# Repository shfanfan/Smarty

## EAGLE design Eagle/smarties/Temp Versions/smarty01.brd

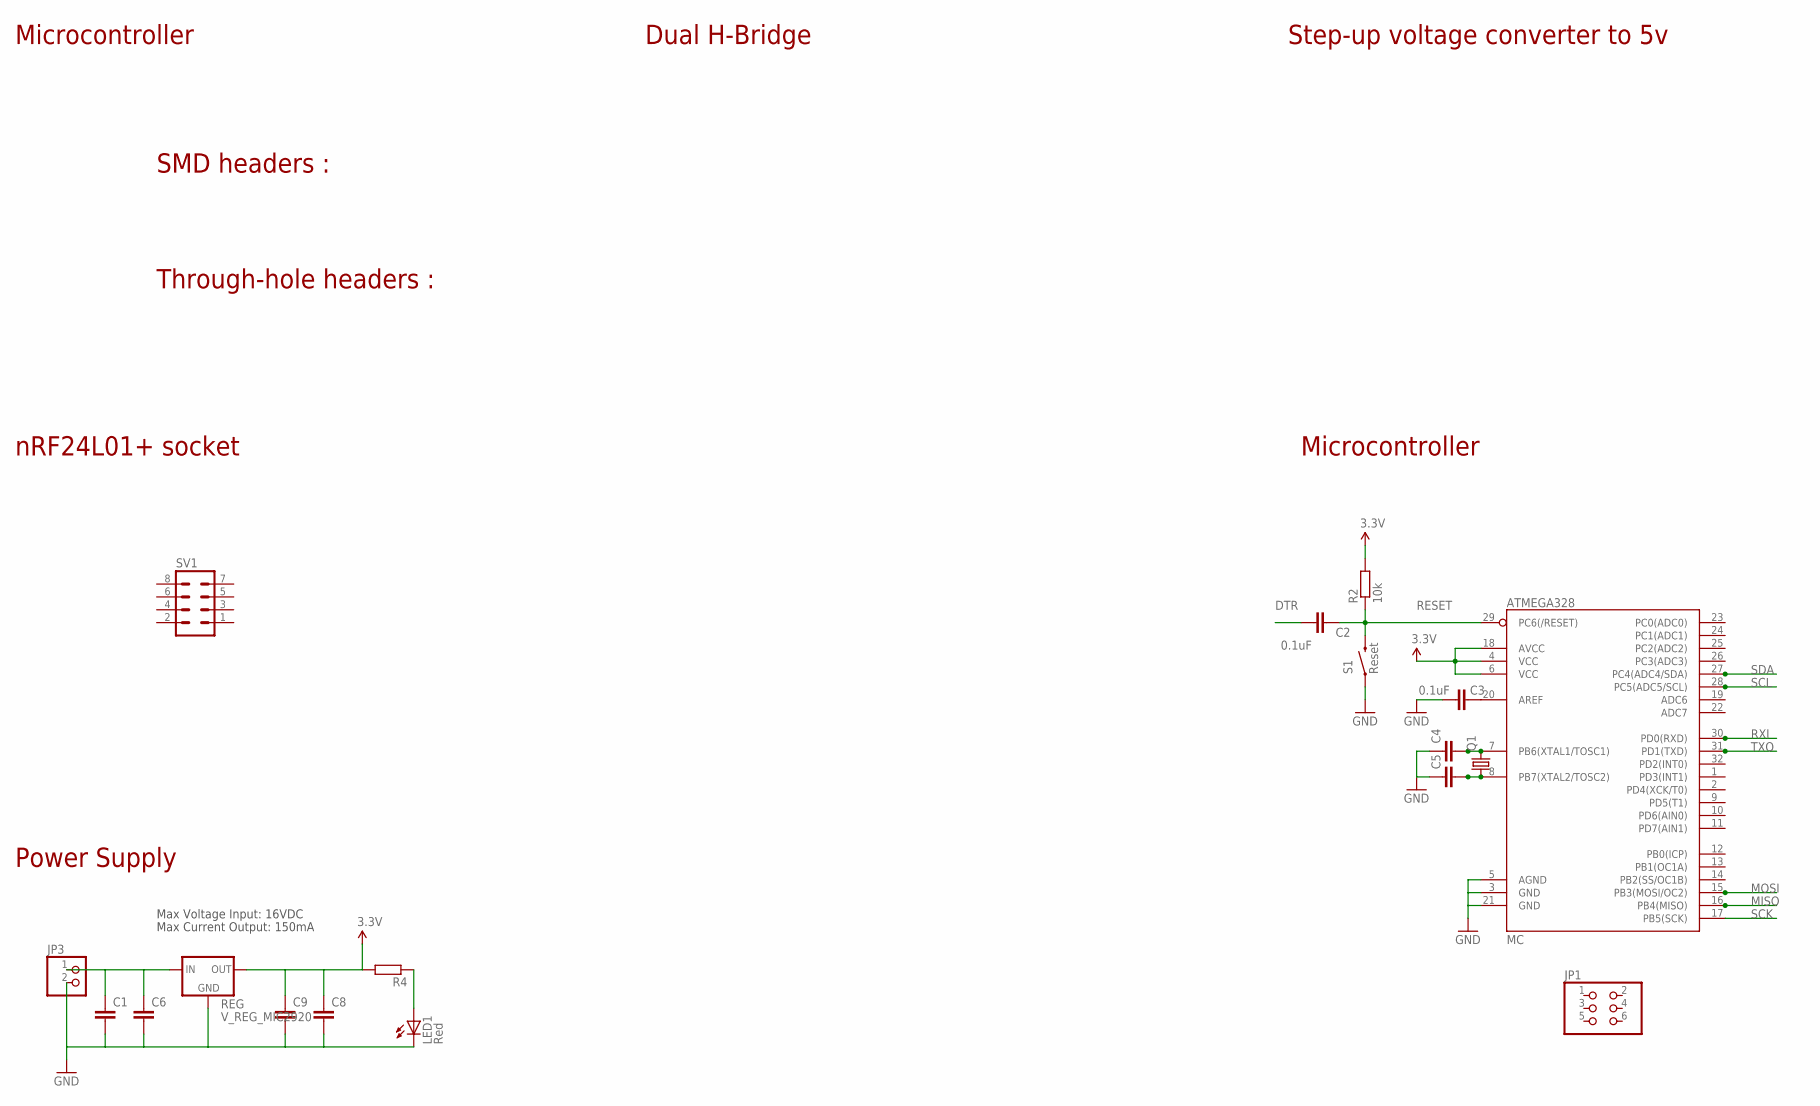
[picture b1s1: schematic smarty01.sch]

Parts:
C1, C4, C5, C6, C8, C9: C-EUC0805; C0805
C2, C3: 0.1uF; C0805
JP1: PINHD-2X03_2.54-SMD; 2X03SMD
JP3: PINHD-1X2; 1X02
LED1: Red; LED-0603
MC: ATMEGA328; TQFP32-08
Q1: CRYSTALHC49UP; HC49UP
R2: 10k; R0805
R4: R-EU_R0805; R0805
REG: V_REG_MIC2920; SOT223
S1: Reset; TACTILE_SWITCH_SMD
SV1: MA04-2

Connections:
3.3V: C8.1, C9.1, MC.4 (VCC), MC.6 (VCC), MC.18 (AVCC), R2.2, R4.2, REG.3 (OUT)
DTR: C2.1
GND: C1.2, C3.2, C4.1, C5.1, C6.2, C8.2, C9.2, JP3.2, LED1.C, MC.3 (GND), MC.5 (AGND), MC.21 (GND), REG.2 (GND), S1.1
MISO: MC.16 (PB4(MISO))
MOSI: MC.15 (PB3(MOSI/OC2))
unnamed: C3.1, MC.20 (AREF)
unnamed: C4.2, MC.7 (PB6(XTAL1/TOSC1)), Q1.2
unnamed: C5.2, MC.8 (PB7(XTAL2/TOSC2)), Q1.1
unnamed: LED1.A, R4.1
unnamed: C1.1, C6.1, JP3.1, REG.1 (IN)
RESET: C2.2, MC.29 (PC6(/RESET)), R2.1, S1.3 (2)
RXI: MC.30 (PD0(RXD))
SCK: MC.17 (PB5(SCK))
SCL: MC.28 (PC5(ADC5/SCL))
SDA: MC.27 (PC4(ADC4/SDA))
TXO: MC.31 (PD1(TXD))

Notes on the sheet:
Power Supply
Microcontroller
Max Voltage Input: 16VDC
Max Current Output: 150mA
Step-up voltage converter to 5v
Dual H-Bridge
SMD headers :
Through-hole headers :
nRF24L01+ socket

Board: 2 copper layers, 20 parts (0 on the bottom side), 8 nets, no tracks yet.

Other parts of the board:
U$1, U$2: 2,8

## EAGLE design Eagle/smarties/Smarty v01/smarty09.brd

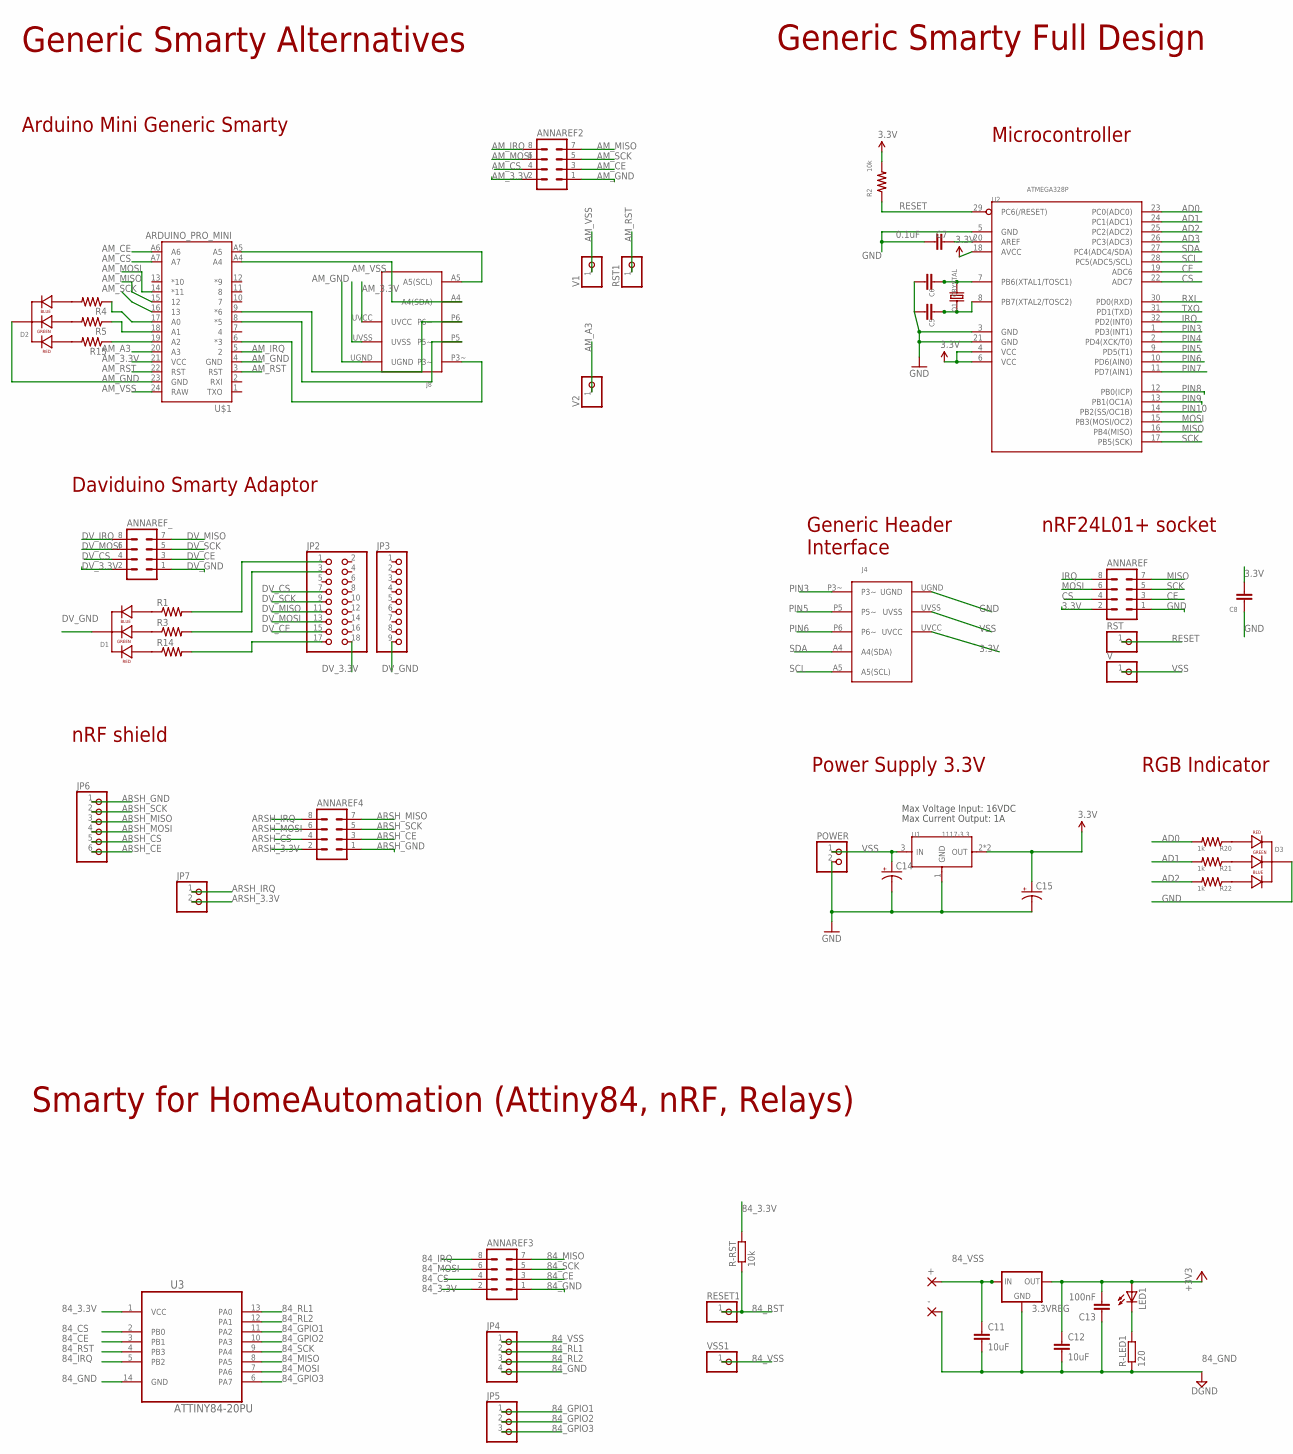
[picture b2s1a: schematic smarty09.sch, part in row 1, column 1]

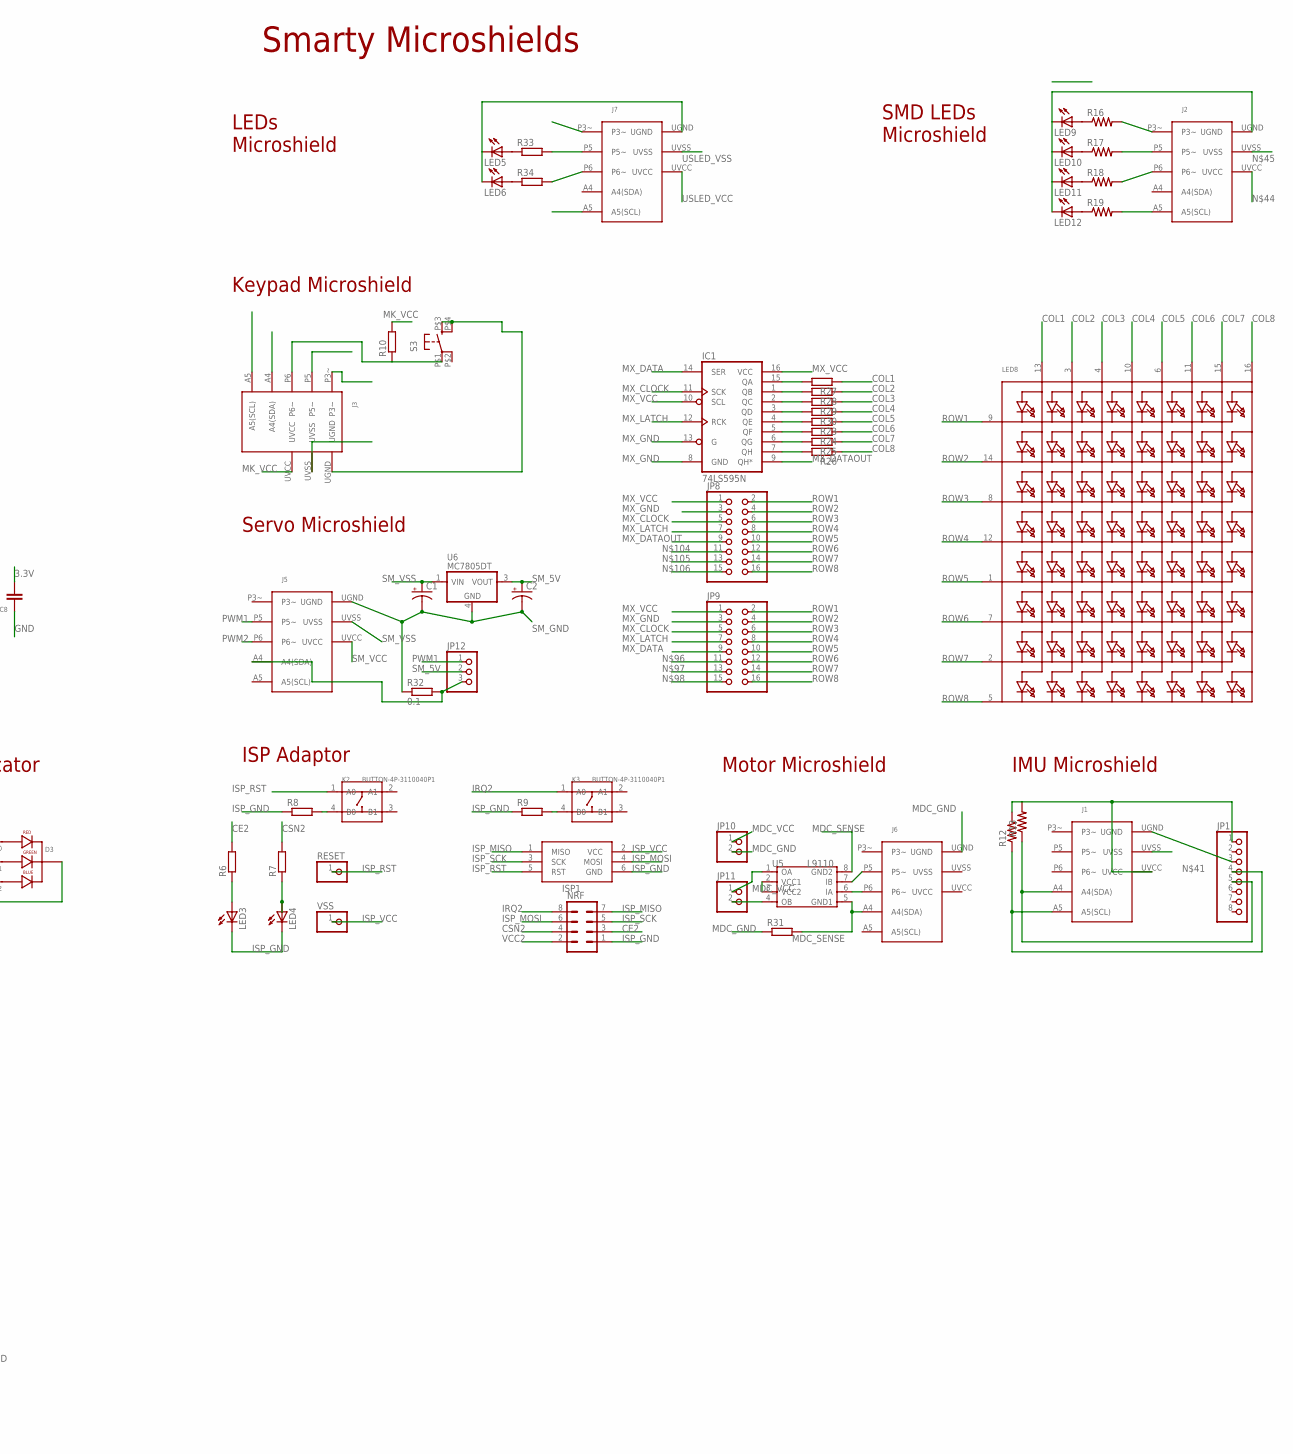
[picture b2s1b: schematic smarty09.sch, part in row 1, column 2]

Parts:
3.3VREG: 78LXX
+: 2,54/1,1
-: 2,54/1,1
ANNAREF, ANNAREF2, ANNAREF3, ANNAREF4: MA04-2
ANNAREF_: MA04-2
C1, C2, C14, C15: CAP_POL6032; EIA6032
C5, C6, C8: CAP1206; 1206
C7: 0.1uF; 1206
C11, C12: 10uF; C025-050X050
C13: 100nF; C050-024X044
D1, D2, D3: LED-RGB-CC-THRUCLEAR; LED-RGB-THRU
IC1: 74LS595N; DIL16
ISP1: AVRISP-6; AVRISP
J1, J2, J3, J4, J5, J6, J7, J8: SMARTY-USHIELD; SMARTY-USHIELD-2.54
JP1: PINHD-1X8BIG; 1X08-BIG
JP2: PINHD-2X9-BIG; 2X09-BIG
JP3: PINHD-1X9; 1X09-BIG
JP4: PINHD-1X4; 1X04
JP5: PINHD-1X3; 1X03
JP6: PINHD-1X6; 1X06
JP7, JP10, JP11: PINHD-1X2; 1X02
JP8, JP9: PINHD-2X8; 2X08
JP12: PINHD-1X3/90; 1X03/90
K2, K3: BUTTON-4P-3110040P1; 4P-6.0X6.0X5.0H
LED1, LED3, LED4, LED5, LED6: LED3MM
LED8: SEGMENT_8X8_ROWCATHODEM12A881UR; SEGMENT_BL-M12A881UR
LED9, LED10, LED11, LED12: LEDCHIPLED_1206; CHIPLED_1206
NRF: MA04-2
POWER: PINHD-1X2; 1X02
Q1: CRYSTAL; 2P-SMD-5.0X3.2
R1, R3, R14: R-US_0204/2V; 0204V
R2: 10k; 1206
R4, R5, R15: R-US_0207/2V; 0207/2V
R6, R7, R8, R9, R23, R24, R25, R26, R27, R28, R30: R-EU_0204/2V; 0204V
R10, R29: R-EU_0204/7; 0204/7
R12, R13, R16, R17, R18, R19: RESISTOR1206; 1206
R20, R21, R22: 1k; 1206
R31: R-EU_R1206; R1206
R32: 0.1; R1206
R33, R34: R-EU_0207/2V; 0207/2V
R-LED1: 120; 0204V
R-RST: 10k; 0204V
RESET, RESET1: PINHD-1X1; 1X01
RST, RST1: PINHD-1X1; 1X01
S3: TAC_SWITCHKSA_SEALED; KSA_SEALED_TAC_SWITCH
U1: 1117-3.3; SOT89
U2: ATMEGA328P; TQFP32
U3: ATTINY84-20PU; DIP254P762X533-14
U5: L9110; SOIC8
U6: MC7805DT; DPAK-3
U$1: ARDUINO_PRO_MINI
V, V1, V2: PINHD-1X1; 1X01
VSS, VSS1: PINHD-1X1; 1X01

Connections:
3.3V: ANNAREF.2, C8.1, C15.P$1 (+), J4.UVCC, R2.2, U1.2 (OUT), U1.4 (OUT), U2.4 (VCC), U2.6 (VCC), U2.18 (AVCC)
84_3.3V: 3.3VREG.OUT, ANNAREF3.2, C12.1, C13.2, LED1.A, R-RST.2, U3.1 (VCC)
84_CE: ANNAREF3.3, U3.3 (PB1)
84_CS: ANNAREF3.4, U3.2 (PB0)
84_GND: 3.3VREG.GND, -.1, ANNAREF3.1, C11.2, C12.2, C13.1, JP4.4, R-LED1.1, U3.14 (GND)
84_GPIO1: JP5.1, U3.11 (PA2)
84_GPIO2: JP5.2, U3.10 (PA3)
84_GPIO3: JP5.3, U3.6 (PA7)
84_IRQ: ANNAREF3.8, U3.5 (PB2)
84_MISO: ANNAREF3.7, U3.8 (PA5)
84_MOSI: ANNAREF3.6, U3.7 (PA6)
84_RL1: JP4.2, U3.13 (PA0)
84_RL2: JP4.3, U3.12 (PA1)
84_RST: R-RST.1, RESET1.1, U3.4 (PB3)
84_SCK: ANNAREF3.5, U3.9 (PA4)
84_VSS: 3.3VREG.IN, +.1, C11.1, JP4.1, VSS1.1
AD0: R20.2, U2.23 (PC0(ADC0))
AD1: R21.2, U2.24 (PC1(ADC1))
AD2: R22.2, U2.25 (PC2(ADC2))
AD3: U2.26 (PC3(ADC3))
AM_3.3V: ANNAREF2.2, J8.UVCC, U$1.21 (VCC)
AM_A3: U$1.20 (A3), V2.1
AM_CE: ANNAREF2.3, U$1.A6
AM_CS: ANNAREF2.4, U$1.A7
AM_GND: ANNAREF2.1, D2.2 (CATHODE), J8.UGND, U$1.4 (GND), U$1.23 (GND)
AM_IRQ: ANNAREF2.8, U$1.5 (2)
AM_MISO: ANNAREF2.7, U$1.15 (12)
AM_MOSI: ANNAREF2.6, U$1.14 (*11)
AM_RST: RST1.1, U$1.3 (RST), U$1.22 (RST)
AM_SCK: ANNAREF2.5, U$1.16 (13)
AM_VSS: J8.UVSS, U$1.24 (RAW), V1.1
ARSH_3.3V: ANNAREF4.2, JP7.2
ARSH_CE: ANNAREF4.3, JP6.6
ARSH_CS: ANNAREF4.4, JP6.5
ARSH_GND: ANNAREF4.1, JP6.1
ARSH_IRQ: ANNAREF4.8, JP7.1
ARSH_MISO: ANNAREF4.7, JP6.3
ARSH_MOSI: ANNAREF4.6, JP6.4
ARSH_SCK: ANNAREF4.5, JP6.2
CE: ANNAREF.3, U2.19 (ADC6)
CE2: NRF.3, R6.2
COL1: LED8.13 (A1), R27.1
COL2: LED8.3 (A2), R28.1
COL3: LED8.4 (A3), R29.1
COL4: LED8.10 (A4), R30.1
COL5: LED8.6 (A5), R23.1
COL6: LED8.11 (A6), R24.1
COL7: LED8.15 (A7), R25.1
COL8: LED8.16 (A8), R26.1
CS: ANNAREF.4, U2.22 (ADC7)
CSN2: NRF.4, R7.2
DV_3.3V: ANNAREF_.2, JP2.18
DV_CE: ANNAREF_.3, JP2.15
DV_CS: ANNAREF_.4, JP2.7
DV_GND: ANNAREF_.1, D1.2 (CATHODE), JP3.9
DV_IRQ: ANNAREF_.8
DV_MISO: ANNAREF_.7, JP2.11
DV_MOSI: ANNAREF_.6, JP2.13
DV_SCK: ANNAREF_.5, JP2.9
GND: ANNAREF.1, C5.1, C6.1, C7.2, C8.2, C14.P$2 (-), C15.P$2 (-), D3.2 (CATHODE), J4.UGND, POWER.2, U1.1 (GND), U2.3 (GND), U2.5 (GND), U2.21 (GND)
IA: J6.P6 (P6~), U5.6 (IA)
IB: J6.P5 (P5~), U5.7 (IB)
IRQ: ANNAREF.8, U2.32 (PD2(INT0))
IRQ2: K3.1 (A0), NRF.8
ISP_GND: ISP1.6 (GND), LED3.K (C), LED4.K (C), NRF.1, R8.1, R9.1
ISP_MISO: ISP1.1 (MISO), NRF.7
ISP_MOSI: ISP1.4 (MOSI), NRF.6
ISP_RST: ISP1.5 (RST), K2.1 (A0), RESET.1
ISP_SCK: ISP1.3 (SCK), NRF.5
ISP_VCC: ISP1.2 (VCC), VSS.1
LD1: J2.P3~, R16.2
LD2: J2.P5 (P5~), R17.2
LD3: J2.P6 (P6~), R18.2
LD4: J7.P3~
LD5: J7.P5 (P5~), R33.2
LD6: J7.P6 (P6~), R34.2
MDC_GND: J6.UGND, JP10.2, R31.1
MDC_SENSE: J6.A4 (A4(SDA)), R31.2, U5.5 (GND1), U5.8 (GND2)
MDC_VCC: JP10.1, U5.2 (VCC1), U5.3 (VCC2)
MISO: ANNAREF.7, U2.16 (PB4(MISO))
MK_VCC: J3.UVCC, R10.2
MOSI: ANNAREF.6, U2.15 (PB3(MOSI/OC2))
MX_CLOCK: IC1.11 (SCK), JP8.5, JP9.5
MX_DATA: IC1.14 (SER), JP9.9
MX_DATAOUT: IC1.9 (QH*), JP8.9
MX_GND: IC1.8 (GND), IC1.13 (G), JP8.3, JP9.3
MX_LATCH: IC1.12 (RCK), JP8.7, JP9.7
MX_VCC: IC1.10 (SCL), IC1.16 (VCC), JP8.1, JP9.1
unnamed: C7.1, U2.20 (AREF)
unnamed: C6.2, Q1.2, U2.7 (PB6(XTAL1/TOSC1))
unnamed: JP11.1, U5.1 (OA)
unnamed: C5.2, Q1.1, U2.8 (PB7(XTAL2/TOSC2))
unnamed: JP11.2, U5.4 (OB)
unnamed: J8.A4 (A4(SDA)), U$1.A4
unnamed: J8.A5 (A5(SCL)), U$1.A5
unnamed: K3.4 (B0), R9.2
unnamed: K2.4 (B0), R8.2
unnamed: LED3.A, R6.1
unnamed: LED4.A, R7.1
unnamed: D1.4 (BLUE_CATHODE), R1.1
unnamed: D1.3 (GREEN_CATHODE), R3.1
unnamed: D1.1 (RED_CATHODE), R14.1
unnamed: JP2.17, R14.2
unnamed: J3.P6 (P6~), R10.1, S3.P$1 (1)
unnamed: J3.UGND, S3.P$3 (3), S3.P$4 (4)
unnamed: J1.UVCC, JP1.1, R12.2, R13.2
unnamed: J1.UGND, JP1.3
unnamed: J1.A5 (A5(SCL)), JP1.4, R12.1
unnamed: J1.A4 (A4(SDA)), JP1.5, R13.1
unnamed: D2.4 (BLUE_CATHODE), R4.2
unnamed: R4.1, U$1.17 (A0)
unnamed: D2.3 (GREEN_CATHODE), R5.2
unnamed: JP2.3, R3.2
unnamed: JP2.1, R1.2
unnamed: IC1.15 (QA), R27.2
unnamed: IC1.1 (QB), R28.2
unnamed: IC1.2 (QC), R29.2
unnamed: J8.P6 (P6~), U$1.9 (*6)
unnamed: J8.P5 (P5~), U$1.8 (*5)
unnamed: IC1.3 (QD), R30.2
unnamed: J8.P3~, U$1.6 (*3)
unnamed: IC1.4 (QE), R23.2
unnamed: IC1.5 (QF), R24.2
unnamed: IC1.6 (QG), R25.2
unnamed: R5.1, U$1.18 (A1)
unnamed: D2.1 (RED_CATHODE), R15.2
unnamed: D3.1 (RED_CATHODE), R20.1
unnamed: J2.A5 (A5(SCL)), R19.2
unnamed: IC1.7 (QH), R26.2
unnamed: R15.1, U$1.19 (A2)
unnamed: LED1.K (C), R-LED1.2
unnamed: LED5.A, R33.1
unnamed: LED6.A, R34.1
unnamed: LED9.A, R16.1
unnamed: LED10.A, R17.1
unnamed: LED11.A, R18.1
unnamed: LED12.A, R19.1
unnamed: D3.3 (GREEN_CATHODE), R21.1
unnamed: D3.4 (BLUE_CATHODE), R22.1
unnamed: J2.UGND, LED9.C, LED10.C, LED11.C, LED12.C
unnamed: J5.A4 (A4(SDA)), JP12.3, R32.2
PIN3: J4.P3~, U2.1 (PD3(INT1))
PIN4: U2.2 (PD4(XCK/T0))
PIN5: J4.P5 (P5~), U2.9 (PD5(T1))
PIN6: J4.P6 (P6~), U2.10 (PD6(AIN0))
PIN7: U2.11 (PD7(AIN1))
PIN8: U2.12 (PB0(ICP))
PIN9: U2.13 (PB1(OC1A))
PIN10: U2.14 (PB2(SS/OC1B))
PWM1: J5.P5 (P5~), JP12.1
PWM2: J5.P6 (P6~)
RESET: R2.1, RST.1, U2.29 (PC6(/RESET))
ROW1: JP8.2, JP9.2, LED8.9 (K1)
ROW2: JP8.4, JP9.4, LED8.14 (K2)
ROW3: JP8.6, JP9.6, LED8.8 (K3)
ROW4: JP8.8, JP9.8, LED8.12 (K4)
ROW5: JP8.10, JP9.10, LED8.1 (K5)
ROW6: JP8.12, JP9.12, LED8.7 (K6)
ROW7: JP8.14, JP9.14, LED8.2 (K7)
ROW8: JP8.16, JP9.16, LED8.5 (K8)
RXI: U2.30 (PD0(RXD))
SCK: ANNAREF.5, U2.17 (PB5(SCK))
SCL: J4.A5 (A5(SCL)), U2.28 (PC5(ADC5/SCL))
SDA: J4.A4 (A4(SDA)), U2.27 (PC4(ADC4/SDA))
SM_5V: C2.P$1 (+), JP12.2, U6.3 (VOUT)
SM_GND: C1.P$2 (-), C2.P$2 (-), J5.UGND, R32.1, U6.4 (GND)
SM_VCC: J5.UVCC
SM_VSS: C1.P$1 (+), J5.UVSS, U6.1 (VIN)
TXO: U2.31 (PD1(TXD))
USLED_GND: J7.UGND, LED5.K (C), LED6.K (C)
USLED_VCC: J7.UVCC
USLED_VSS: J7.UVSS
UVCC: J6.UVCC
UVSS: J6.UVSS
VCC2: NRF.2
VSS: C14.P$1 (+), J4.UVSS, POWER.1, U1.3 (IN), V.1

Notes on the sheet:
Power Supply 3.3V
Microcontroller
Max Voltage Input: 16VDC
Max Current Output: 1A
ISP Adaptor
Generic Header Interface
nRF24L01+ socket
RGB Indicator
Servo Microshield
Motor Microshield
Keypad Microshield
nRF shield
Daviduino Smarty Adaptor
Arduino Mini Generic Smarty
IMU Microshield
Generic Smarty Full Design
Smarty Microshields
Generic Smarty Alternatives
Smarty for HomeAutomation (Attiny84, nRF, Relays)
SMD LEDs Microshield
LEDs Microshield

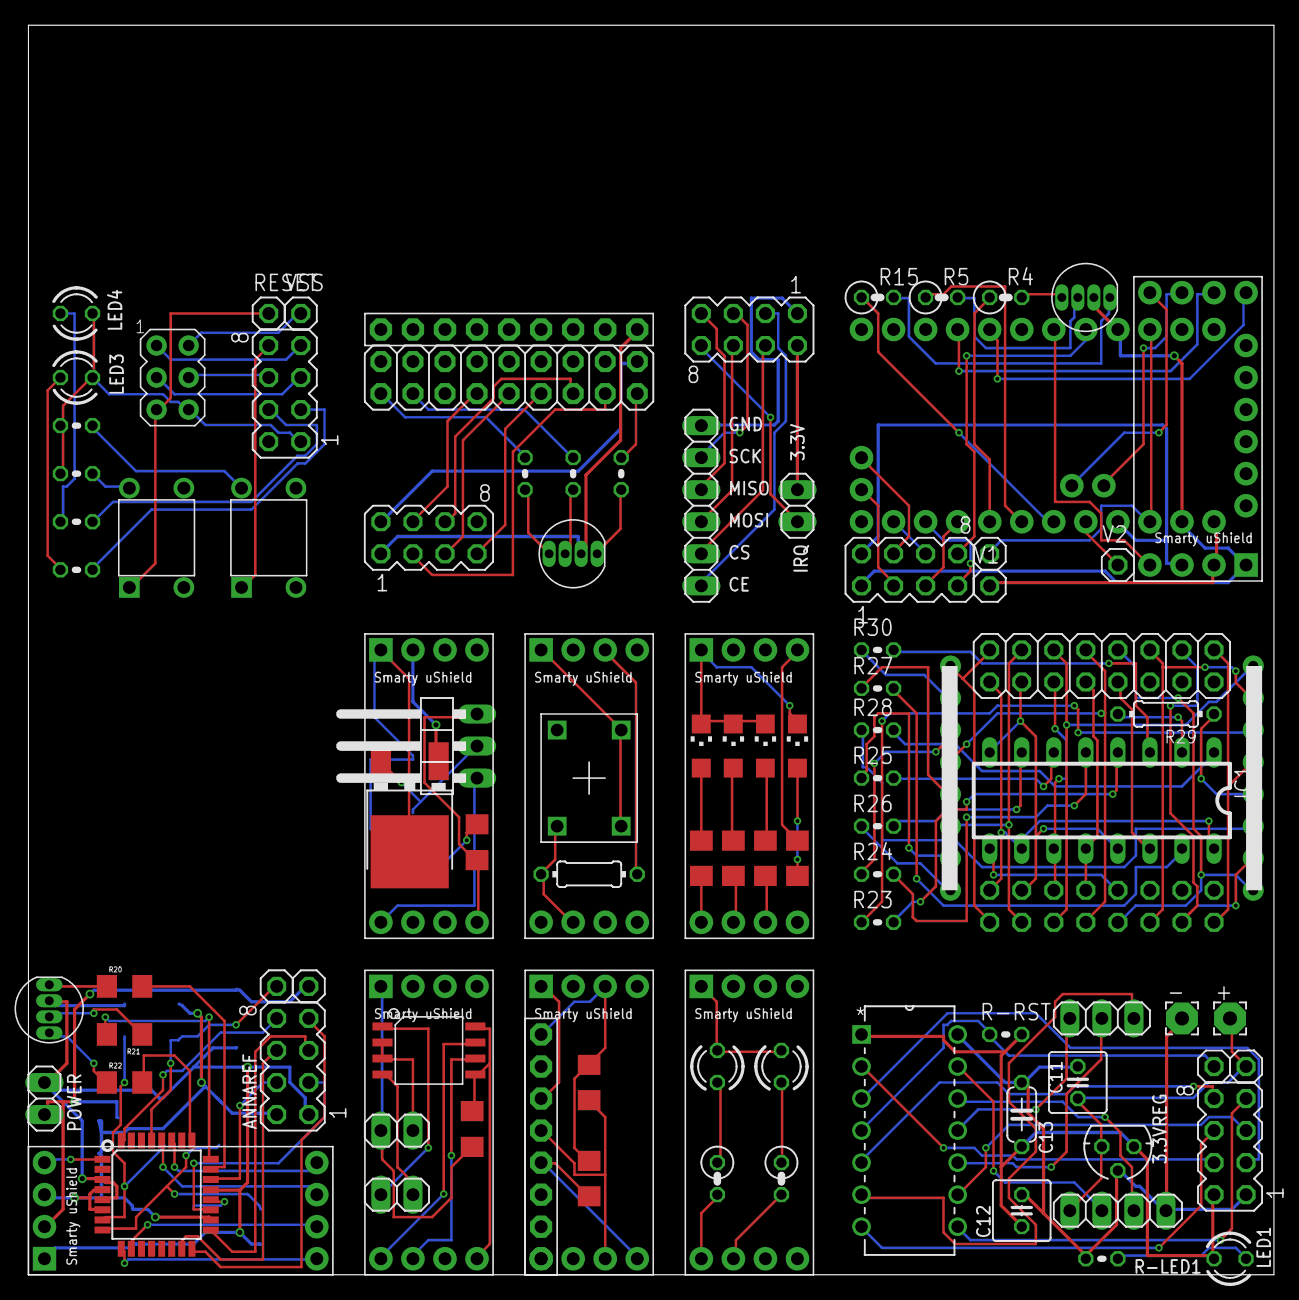
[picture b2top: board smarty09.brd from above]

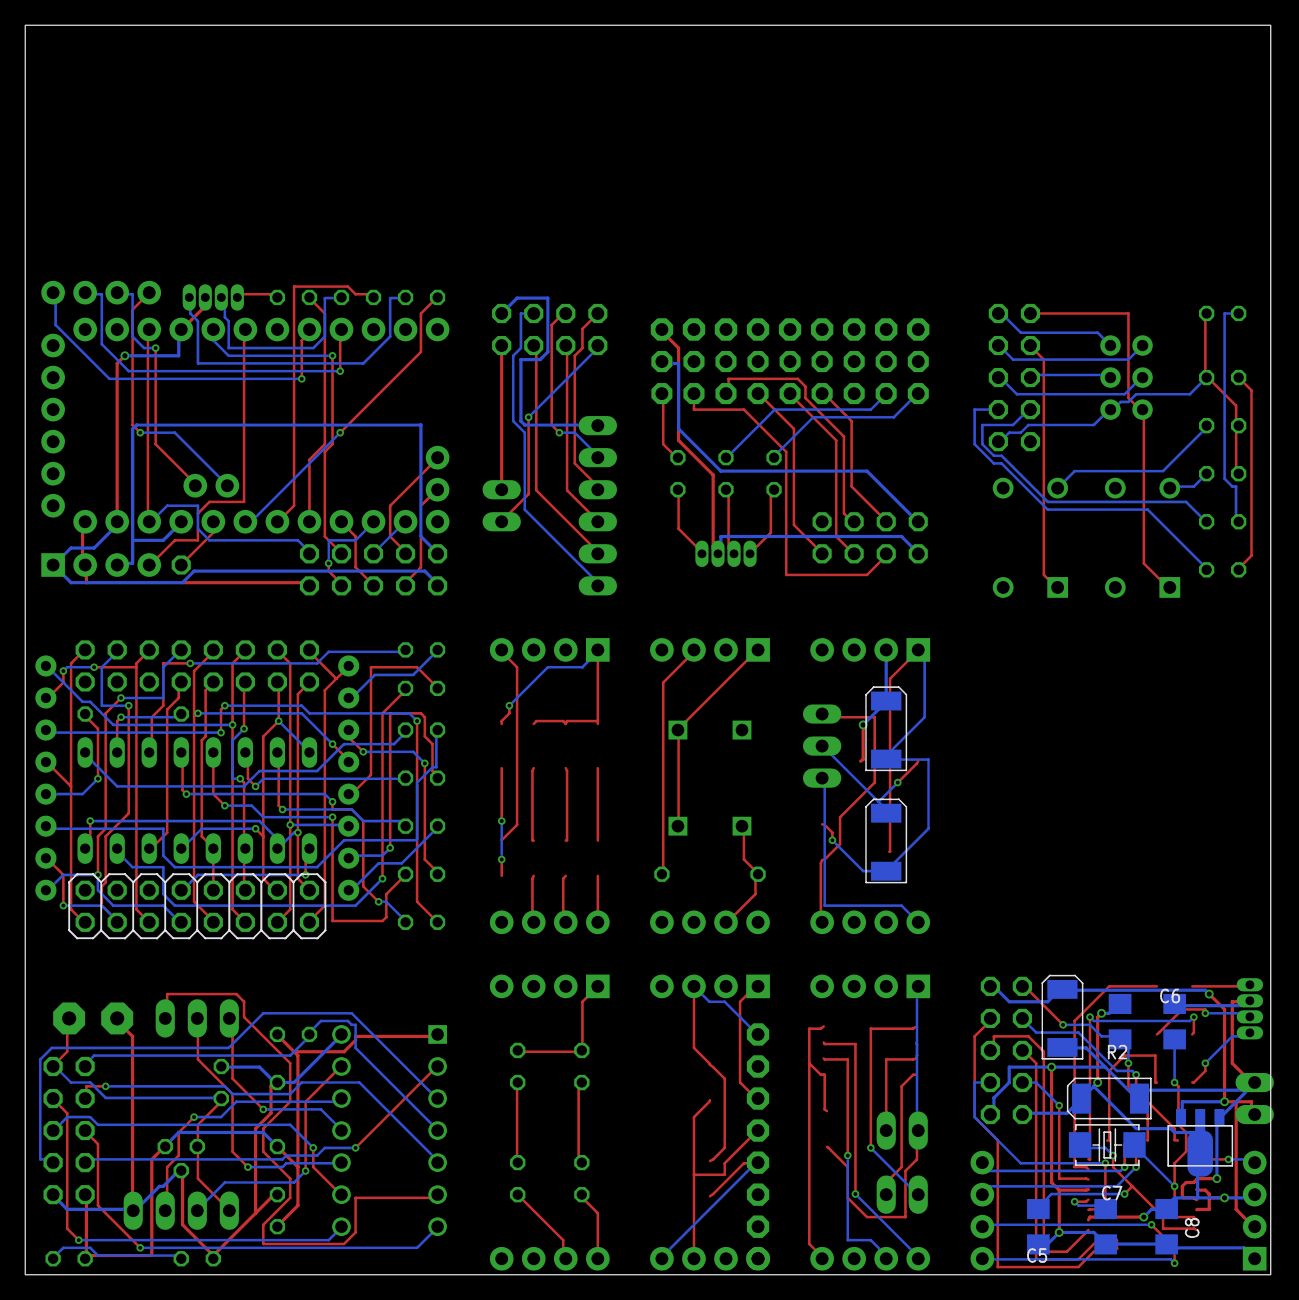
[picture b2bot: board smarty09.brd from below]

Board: 4 copper layers, 98.7 x 99.0 mm, 110 parts (12 on the bottom side), 159 nets.

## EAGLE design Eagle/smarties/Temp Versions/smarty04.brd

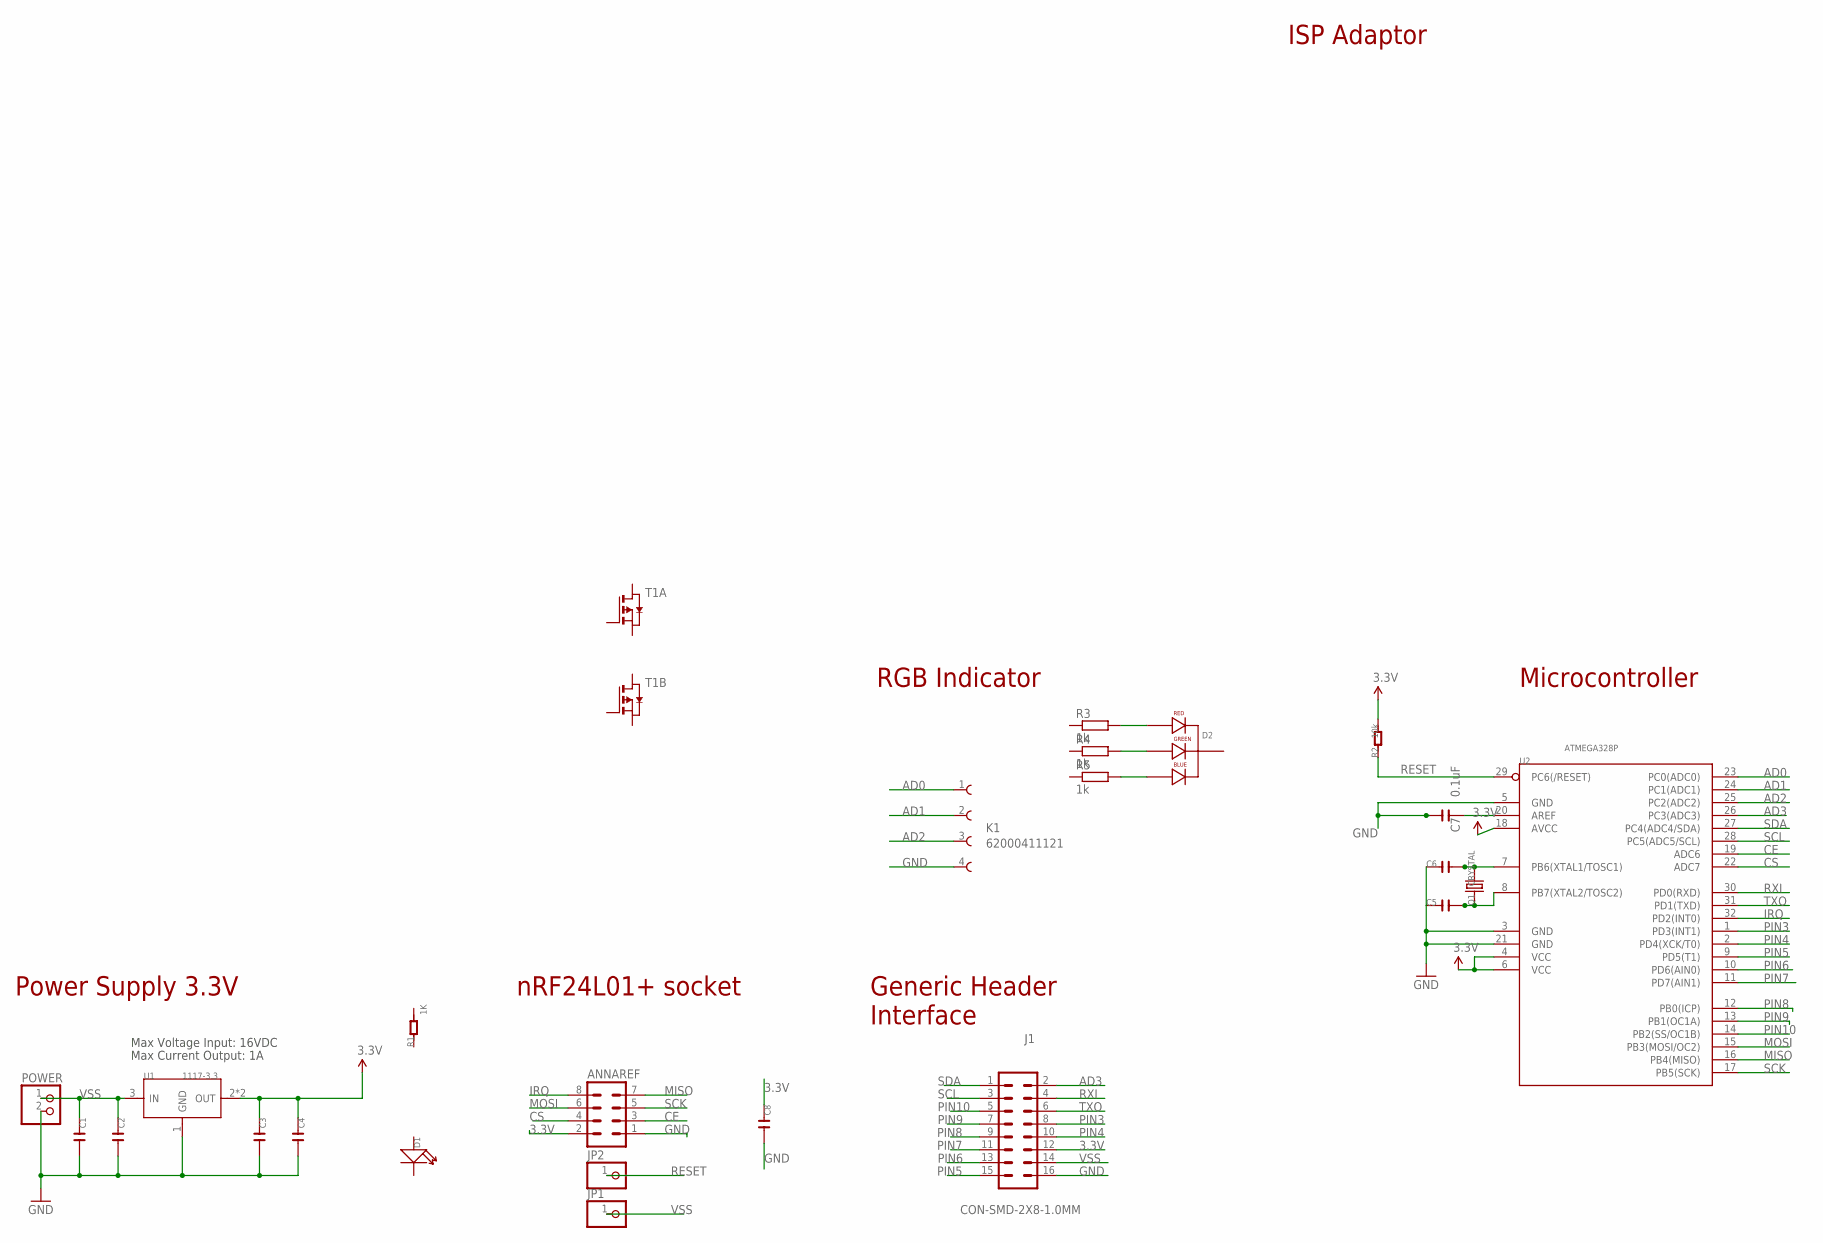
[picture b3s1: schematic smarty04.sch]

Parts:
ANNAREF: MA04-2
C1, C3, C5, C6: C-0603; C0603
C2, C4, C8: C-0805; C0805
C7: 0.1uF; C0805
D1: LED; LED0603
D2: LED-RGB-CC-THRUCLEAR; LED-RGB-THRU
J1: CON-SMD-2X8-1.0MM; SBH100-NBPC-D08
JP1, JP2: PINHD-1X1; 1X01
K1: 62000411121
POWER: PINHD-1X2; 1X02
Q1: CRYSTAL; 2P-SMD-5.0X3.2
R1: 1K; R0603
R2: 10k; R0603
R3, R4, R5: 1k; R0603
T1: PMOS2SO8; SO8
U1: 1117-3.3; SOT89
U2: ATMEGA328P; TQFP32

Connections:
3.3V: ANNAREF.2, C3.1, C4.1, C8.1, J1.12, R2.2, U1.2 (OUT), U1.4 (OUT), U2.4 (VCC), U2.6 (VCC), U2.18 (AVCC)
AD0: K1.1, U2.23 (PC0(ADC0))
AD1: K1.2, U2.24 (PC1(ADC1))
AD2: K1.3, U2.25 (PC2(ADC2))
AD3: J1.2, U2.26 (PC3(ADC3))
CE: ANNAREF.3, U2.19 (ADC6)
CS: ANNAREF.4, U2.22 (ADC7)
GND: ANNAREF.1, C1.2, C2.2, C3.2, C4.2, C5.1, C6.1, C7.2, C8.2, J1.16, K1.4, POWER.2, U1.1 (GND), U2.3 (GND), U2.5 (GND), U2.21 (GND)
IRQ: ANNAREF.8, U2.32 (PD2(INT0))
MISO: ANNAREF.7, U2.16 (PB4(MISO))
MOSI: ANNAREF.6, U2.15 (PB3(MOSI/OC2))
unnamed: C7.1, U2.20 (AREF)
unnamed: C6.2, Q1.2, U2.7 (PB6(XTAL1/TOSC1))
unnamed: D2.1 (RED_CATHODE), R3.2
unnamed: C5.2, Q1.1, U2.8 (PB7(XTAL2/TOSC2))
unnamed: D2.3 (GREEN_CATHODE), R4.2
unnamed: D2.4 (BLUE_CATHODE), R5.2
PIN3: J1.8, U2.1 (PD3(INT1))
PIN4: J1.10, U2.2 (PD4(XCK/T0))
PIN5: J1.15, U2.9 (PD5(T1))
PIN6: J1.13, U2.10 (PD6(AIN0))
PIN7: J1.11, U2.11 (PD7(AIN1))
PIN8: J1.9, U2.12 (PB0(ICP))
PIN9: J1.7, U2.13 (PB1(OC1A))
PIN10: J1.5, U2.14 (PB2(SS/OC1B))
RESET: JP2.1, R2.1, U2.29 (PC6(/RESET))
RXI: J1.4, U2.30 (PD0(RXD))
SCK: ANNAREF.5, U2.17 (PB5(SCK))
SCL: J1.3, U2.28 (PC5(ADC5/SCL))
SDA: J1.1, U2.27 (PC4(ADC4/SDA))
TXO: J1.6, U2.31 (PD1(TXD))
VSS: C1.1, C2.1, J1.14, JP1.1, POWER.1, U1.3 (IN)

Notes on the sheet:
Power Supply 3.3V
Microcontroller
Max Voltage Input: 16VDC
Max Current Output: 1A
ISP Adaptor
Generic Header Interface
nRF24L01+ socket
RGB Indicator

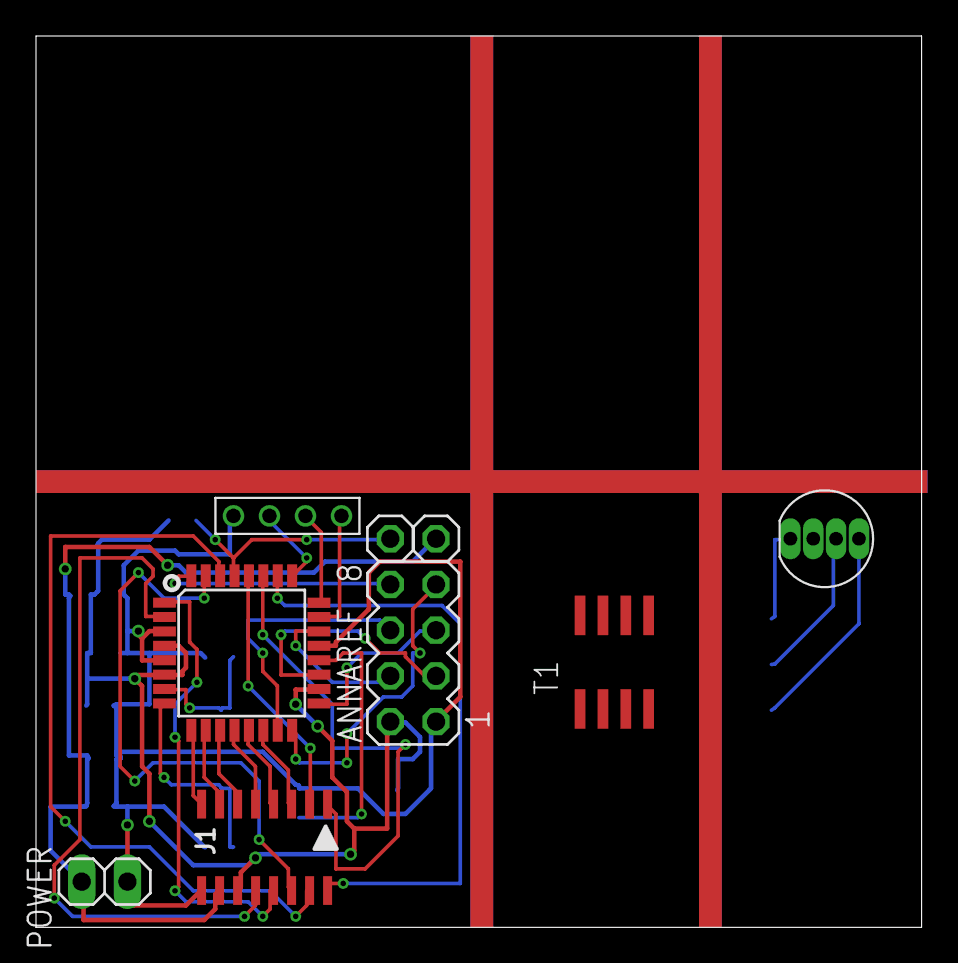
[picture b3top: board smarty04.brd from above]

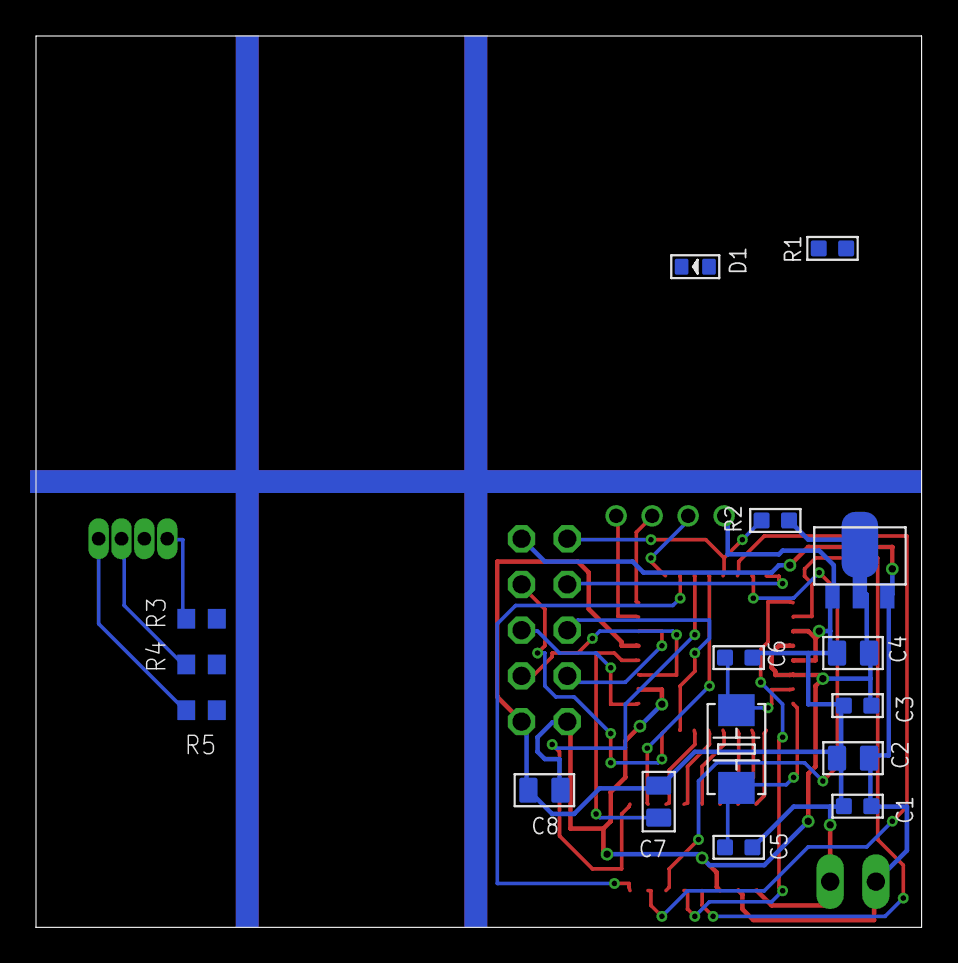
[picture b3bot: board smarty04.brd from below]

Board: 4 copper layers, 49.2 x 49.5 mm, 25 parts (16 on the bottom side), 32 nets.

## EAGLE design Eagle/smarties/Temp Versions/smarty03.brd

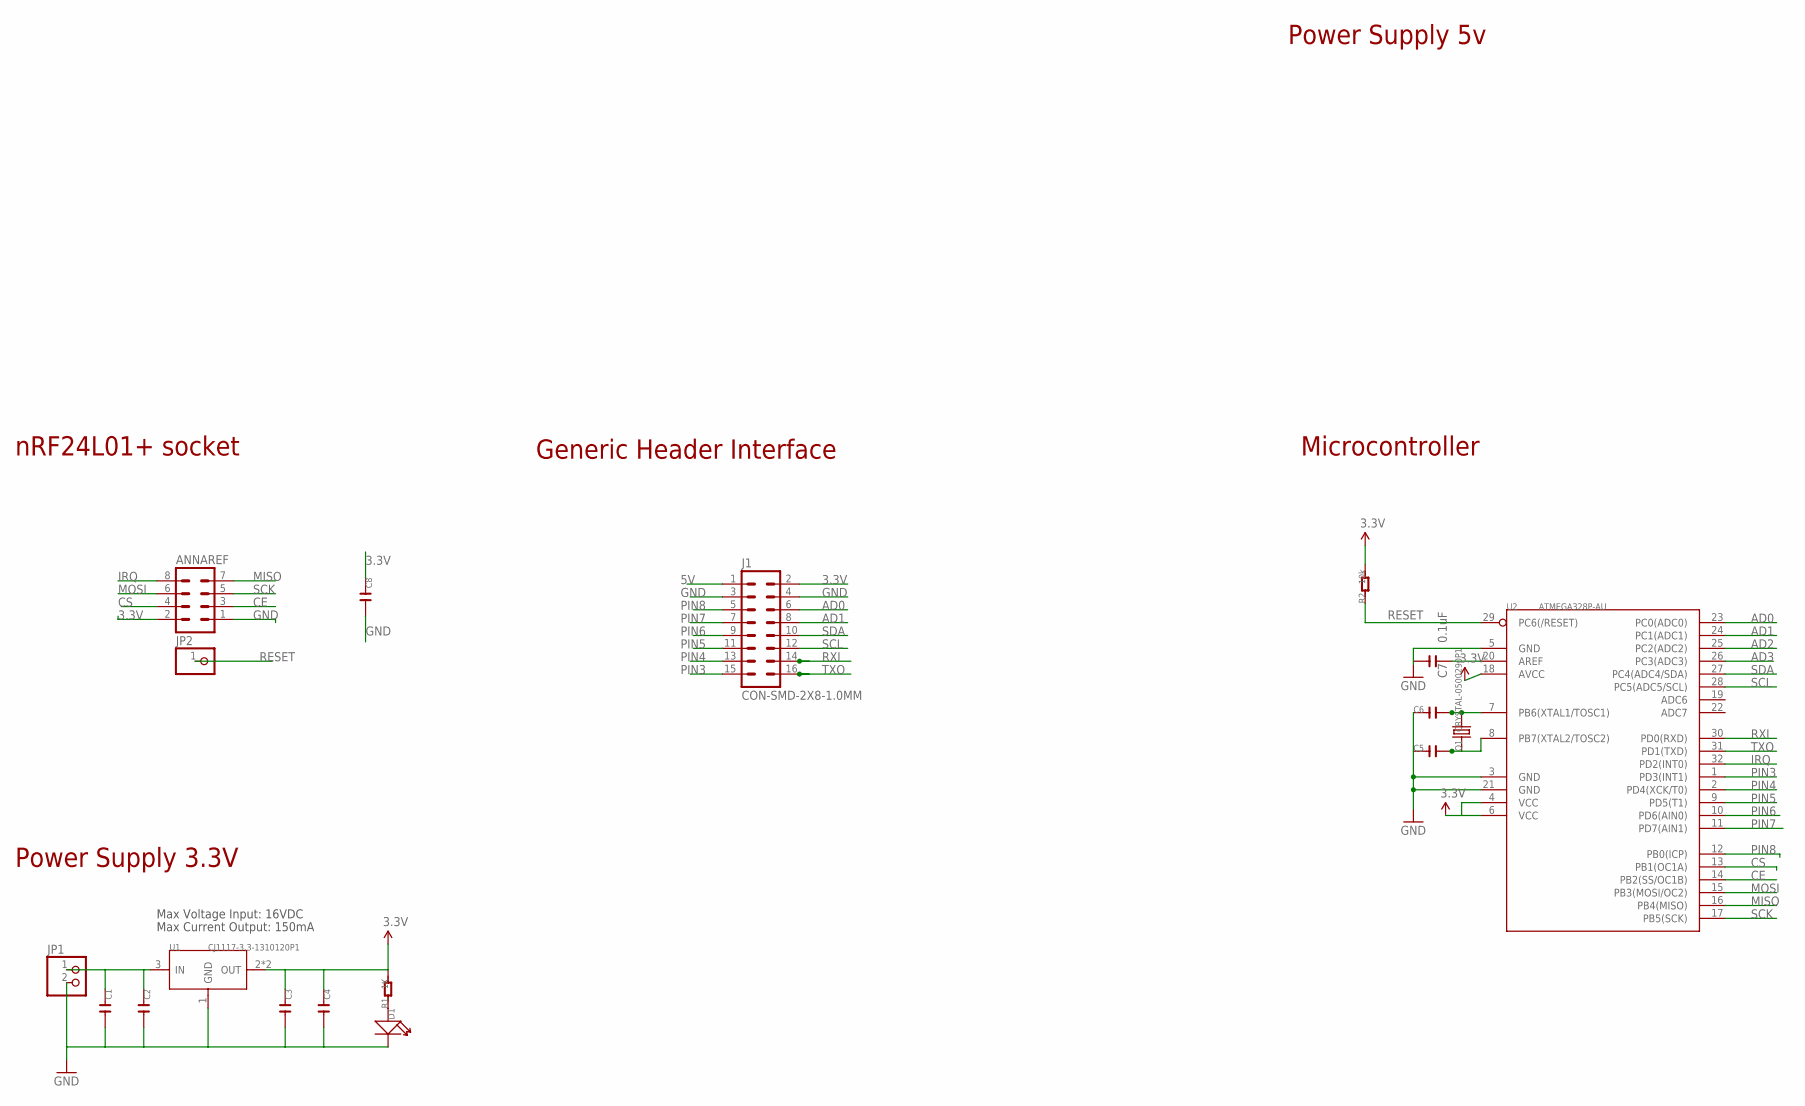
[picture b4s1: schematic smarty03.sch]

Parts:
ANNAREF: MA04-2
C1, C3, C5, C6: C-0603; C0603
C2, C4, C8: C-0805; C0805
C7: 0.1uF; C0805
D1: LED; LED0603
J1: CON-SMD-2X8-1.0MM; SBH100-NBPC-D08
JP1: PINHD-1X2; 1X02
JP2: PINHD-1X1; 1X01
Q1: CRYSTAL-0500290P1; 2P-SMD-5.0X3.2
R1: 1K; R0603
R2: 10k; R0603
U1: CJ1117-3.3-1310120P1; SOT89
U2: ATMEGA328P-AU; TQFP32

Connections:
3.3V: ANNAREF.2, C3.1, C4.1, C8.1, J1.2, R1.2, R2.2, U1.2 (OUT), U1.4 (OUT), U2.4 (VCC), U2.6 (VCC), U2.18 (AVCC)
5V: J1.1
AD0: J1.6, U2.23 (PC0(ADC0))
AD1: J1.8, U2.24 (PC1(ADC1))
AD2: U2.25 (PC2(ADC2))
AD3: U2.26 (PC3(ADC3))
CE: ANNAREF.3, U2.14 (PB2(SS/OC1B))
CS: ANNAREF.4, U2.13 (PB1(OC1A))
GND: ANNAREF.1, C1.2, C2.2, C3.2, C4.2, C5.1, C6.1, C7.2, C8.2, D1.-, J1.3, J1.4, JP1.2, U1.1 (GND), U2.3 (GND), U2.5 (GND), U2.21 (GND)
IRQ: ANNAREF.8, U2.32 (PD2(INT0))
MISO: ANNAREF.7, U2.16 (PB4(MISO))
MOSI: ANNAREF.6, U2.15 (PB3(MOSI/OC2))
unnamed: C7.1, U2.20 (AREF)
unnamed: C6.2, Q1.2, U2.7 (PB6(XTAL1/TOSC1))
unnamed: C5.2, Q1.1, U2.8 (PB7(XTAL2/TOSC2))
unnamed: D1.+, R1.1
unnamed: C1.1, C2.1, JP1.1, U1.3 (IN)
PIN3: J1.15, U2.1 (PD3(INT1))
PIN4: J1.13, U2.2 (PD4(XCK/T0))
PIN5: J1.11, U2.9 (PD5(T1))
PIN6: J1.9, U2.10 (PD6(AIN0))
PIN7: J1.7, U2.11 (PD7(AIN1))
PIN8: J1.5, U2.12 (PB0(ICP))
RESET: JP2.1, R2.1, U2.29 (PC6(/RESET))
RXI: J1.14, U2.30 (PD0(RXD))
SCK: ANNAREF.5, U2.17 (PB5(SCK))
SCL: J1.12, U2.28 (PC5(ADC5/SCL))
SDA: J1.10, U2.27 (PC4(ADC4/SDA))
TXO: J1.16, U2.31 (PD1(TXD))

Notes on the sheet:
Power Supply 3.3V
Microcontroller
Max Voltage Input: 16VDC
Max Current Output: 150mA
Power Supply 5v
Generic Header Interface
nRF24L01+ socket

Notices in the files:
Arduino Code/smarty_backups/Smarty201506202130_david fixes/RF24s.h:
Copyright (C) 2011 J. Coliz <maniacbug@ymail.com>
modify it under the terms of the GNU General Public License
parts and their libraries:
SparkFun-DigitalIC: Licensing: CC v3.0 Share-Alike You are welcome to use this library for commercial purposes.
Wuerth_Elektronik_eiCan_01_Pin__Socked_H: Copyright: Würth Elektronik
